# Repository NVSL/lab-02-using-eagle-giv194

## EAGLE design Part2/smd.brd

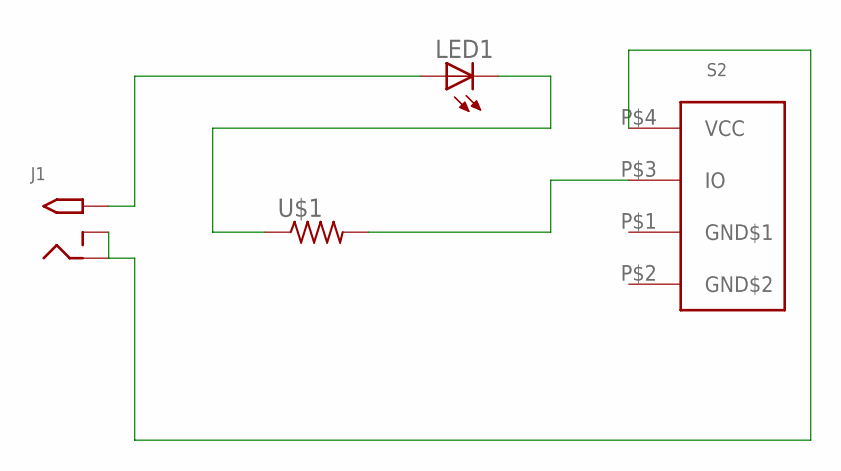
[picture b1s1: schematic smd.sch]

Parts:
J1: 2.1MMJACKTHM; PJ-102A
LED1: LED5MM
S2: BUTTON-TACTILE-SQUARE
U$1: RESISTORTH-1/4W-CARBON; RESAD1160W55L680D260_HS

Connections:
GND$1: S2.P$1 (GND$1)
GND$2: S2.P$2 (GND$2)
unnamed: S2.P$3 (IO), U$1.2
unnamed: LED1.K (C), U$1.1
unnamed: J1.TIP, LED1.A
unnamed: J1.RING, J1.RING_SW, S2.P$4 (VCC)

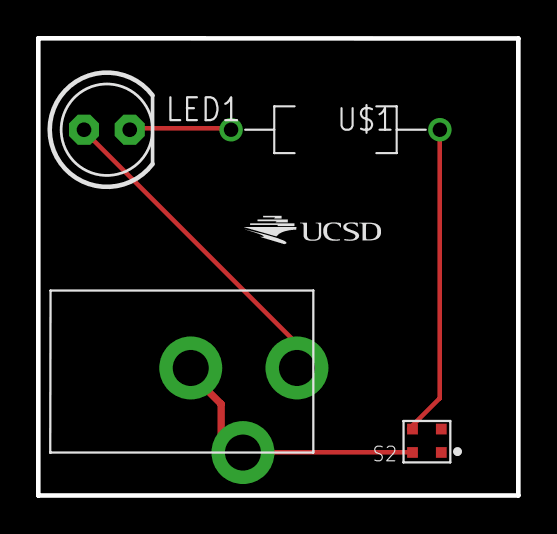
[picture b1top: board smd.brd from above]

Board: 2 copper layers, 26.7 x 25.4 mm, 5 parts (0 on the bottom side), 4 nets.

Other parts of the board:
U$2: UCSD_LOGO

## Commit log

2016-04-07 No Report
2016-04-07 Final Submission
